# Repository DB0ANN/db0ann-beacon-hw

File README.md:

# db0ann-beacon-hw
Hardware documentation of db0ann beacon

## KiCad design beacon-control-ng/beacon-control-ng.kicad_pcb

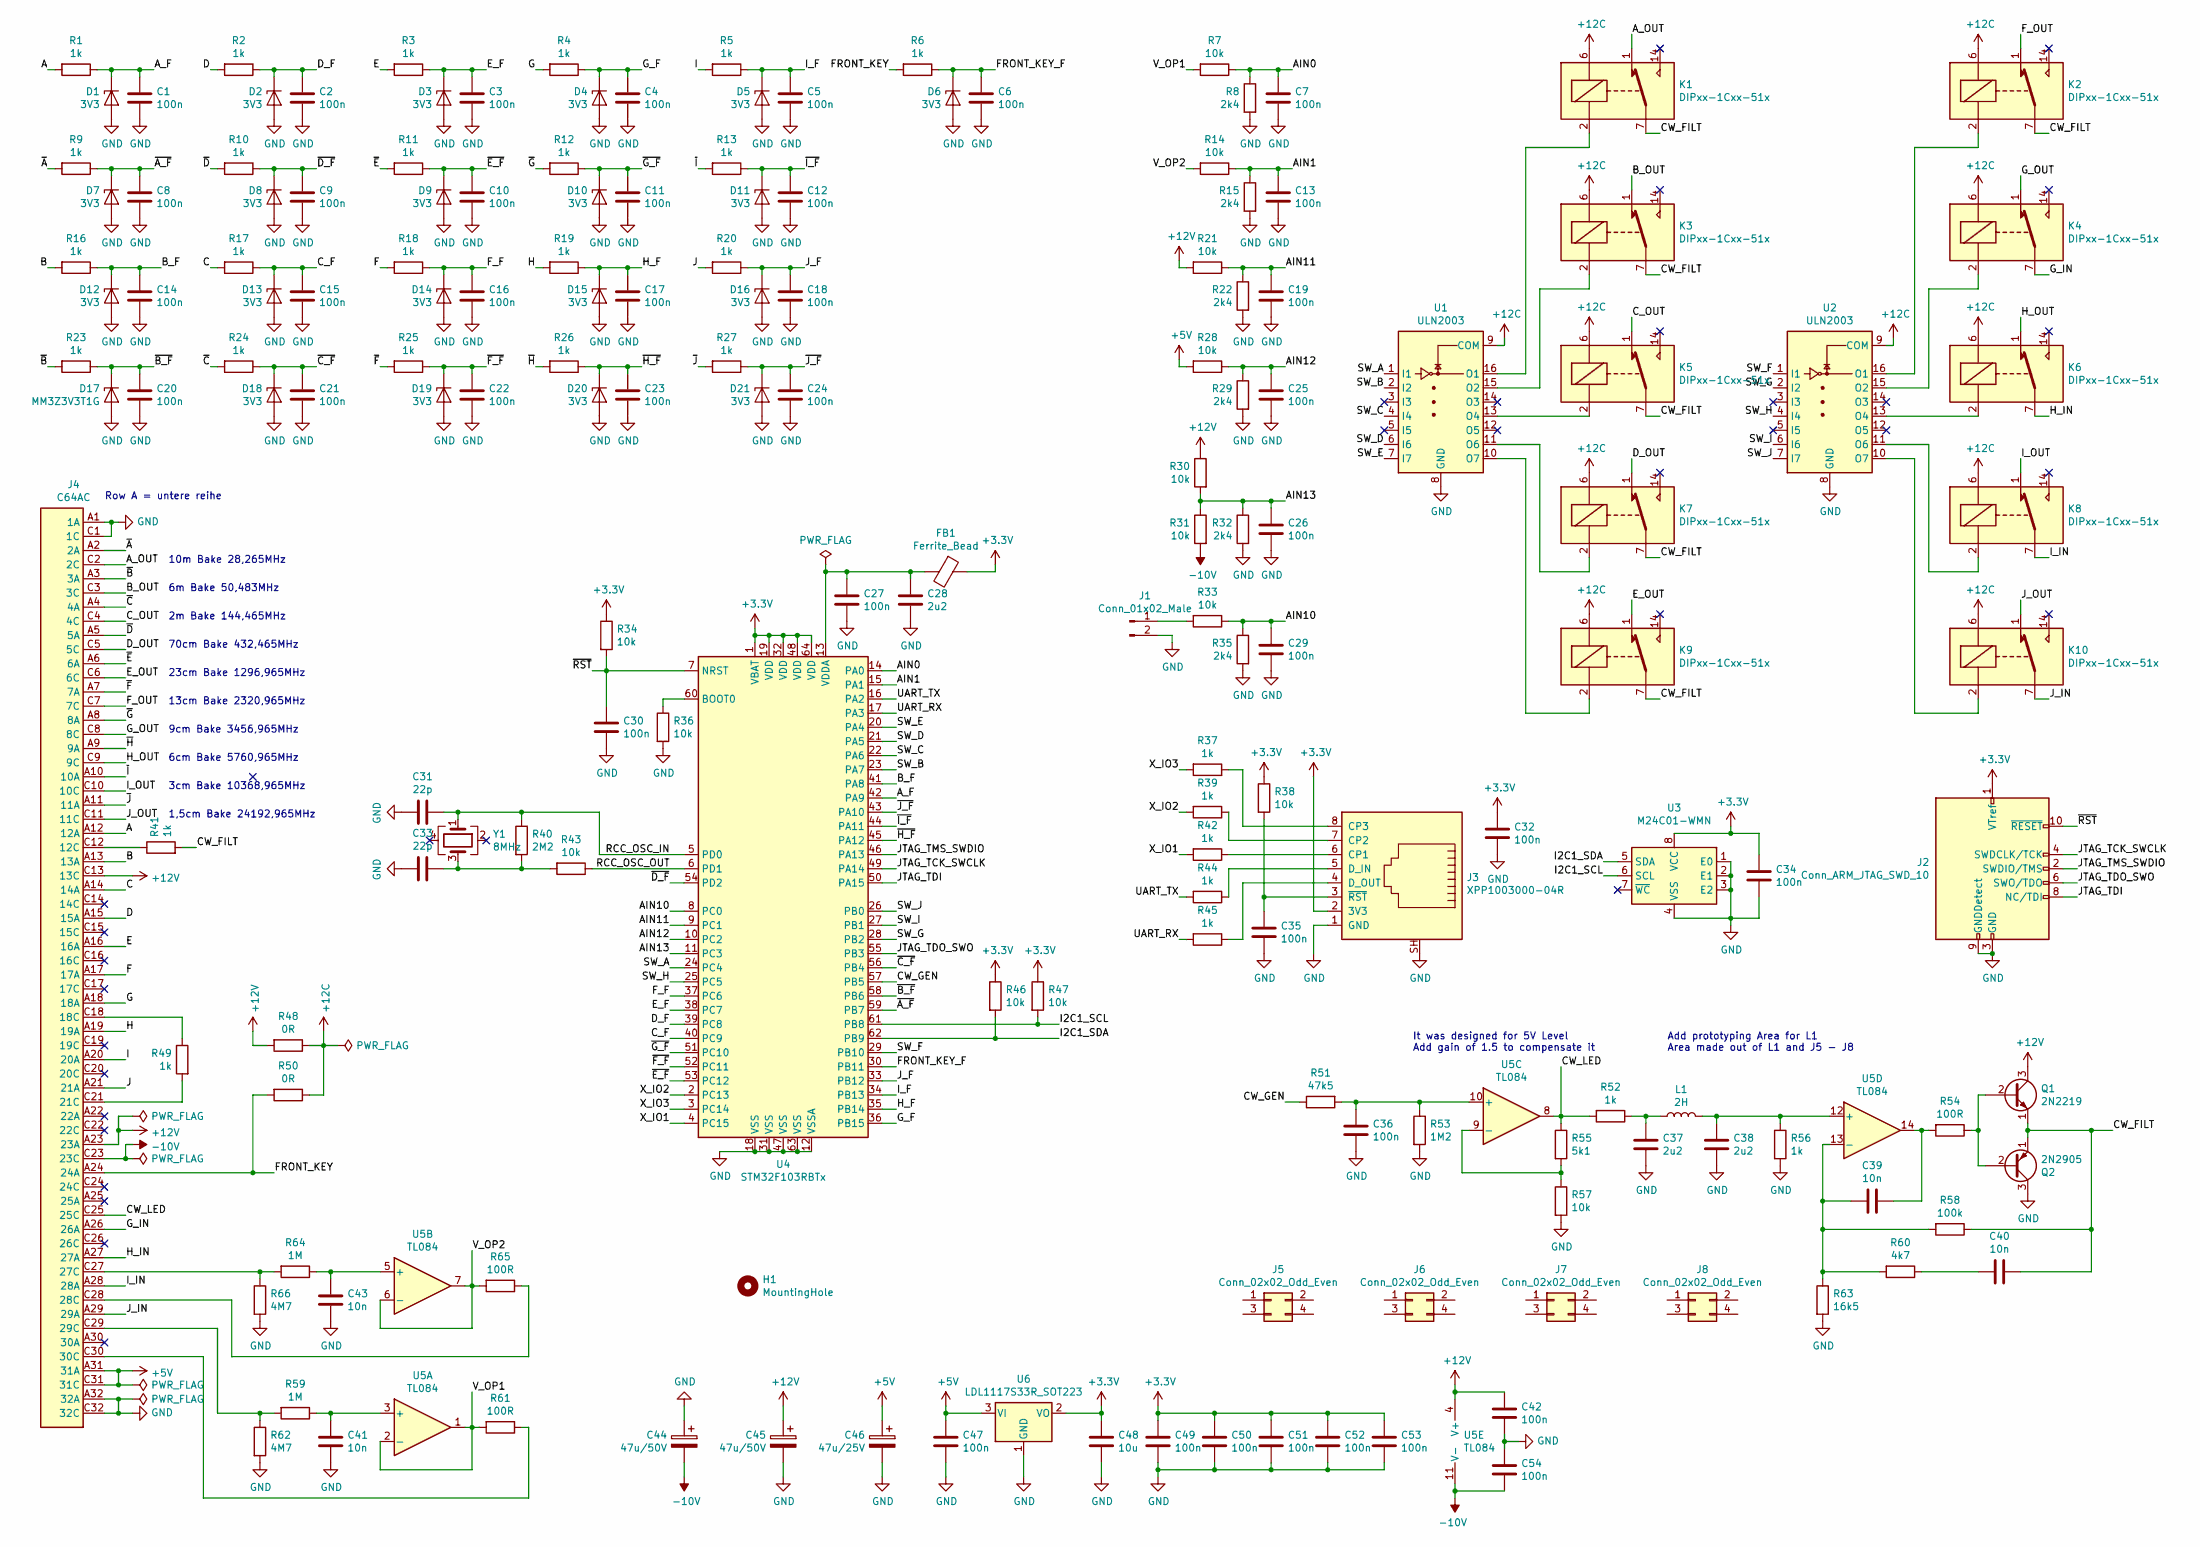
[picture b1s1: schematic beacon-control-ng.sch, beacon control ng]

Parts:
C1, C2, C3, C4, C5, C6, C7, C8, C9, C10, C11, C12, C13, C14, C15, C16, C17, C18, C19, C20, C21, C22, C23, C24, C25, C26, C27, C29, C30, C32, C34, C35, C36, C42, C47, C49, C50, C51, C52, C53, C54: 100n; C_0805_2012Metric
C28, C37, C38: 2u2; C_1206_3216Metric
C31, C33: 22p; C_0805_2012Metric
C39, C40, C41, C43: 10n; C_0805_2012Metric
C44, C45: 47u/50V; CP_Elec_8x10.5
C46: 47u/25V; CP_Elec_8x10.5
C48: 10u; C_1206_3216Metric
D1, D2, D3, D4, D5, D6, D7, D8, D9, D10, D11, D12, D13, D14, D15, D16, D18, D19, D20, D21: 3V3; D_SOD-323
D17: MM3Z3V3T1G; D_SOD-323
FB1: Ferrite_Bead; L_0805_2012Metric
H1: MountingHole; MountingHole_3.2mm_M3
J1: Conn_01x02_Male; PinHeader_1x02_P2.54mm_Vertical
J2: Conn_ARM_JTAG_SWD_10; PinHeader_2x05_P1.27mm_Vertical_SMD
J3: XPP1003000-04R; Lantronix_xPort_Pro
J4: C64AC; DIN41612_C_2x32_Horizontal
J5, J6, J7, J8: Conn_02x02_Odd_Even; PinHeader_2x16_P2.54mm_Vertical
K1, K2, K3, K4, K5, K6, K7, K8, K9, K10: DIPxx-1Cxx-51x; Relay_StandexMeder_DIP_LowProfile
L1: 2H; PinHeader_2x16_P2.54mm_Vertical
Q1: 2N2219; TO-39-3
Q2: 2N2905; TO-39-3
R1, R2, R3, R4, R5, R6, R9, R10, R11, R12, R13, R16, R17, R18, R19, R20, R23, R24, R25, R26, R27, R37, R39, R41, R42, R44, R45, R49, R52, R56: 1k; R_0805_2012Metric
R7, R14, R21, R28, R30, R31, R33, R34, R36, R38, R43, R46, R47, R57: 10k; R_0805_2012Metric
R8, R15, R22, R29, R32, R35: 2k4; R_0805_2012Metric
R40: 2M2; R_0805_2012Metric
R48, R50: 0R; R_0805_2012Metric
R51: 47k5; R_0805_2012Metric
R53: 1M2; R_0805_2012Metric
R54, R61, R65: 100R; R_0805_2012Metric
R55: 5k1; R_0805_2012Metric
R58: 100k; R_0805_2012Metric
R59, R64: 1M; R_0805_2012Metric
R60: 4k7; R_0805_2012Metric
R62, R66: 4M7; R_0805_2012Metric
R63: 16k5; R_0805_2012Metric
U1, U2: ULN2003; SOIC-16_3.9x9.9mm_P1.27mm
U3: M24C01-WMN; SOIC-8_3.9x4.9mm_P1.27mm
U4: STM32F103RBTx; LQFP-64_10x10mm_P0.5mm
U5: TL084; SOIC-14_3.9x8.7mm_P1.27mm
U6: LDL1117S33R_SOT223; SOT-223-3_TabPin2
Y1: 8MHz; Crystal_SMD_EuroQuartz_MQ-4Pin_7.0x5.0mm

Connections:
+3V3: C32.1, C34.1, C48.1, C49.1, C50.1, C51.1, C52.1, C53.1, FB1.1, J2.1 (VTref), J3.2 (3V3), R34.1, R38.1, R46.1, R47.1, U3.8 (VCC), U4.1 (VBAT), U4.19 (VDD), U4.32 (VDD), U4.48 (VDD), U4.64 (VDD), U6.2 (VO)
+5V: C46.1, C47.1, J4.A31 (31A), J4.C31 (31C), R28.2, U6.3 (VI)
+12C: K1.6, K2.6, K3.6, K4.6, K5.6, K6.6, K7.6, K8.6, K9.6, K10.6, R48.1, R50.1, U1.9 (COM), U2.9 (COM)
+12V: C42.1, C45.1, J4.A23 (23A), J4.C13 (13C), Q1.3 (C), R21.2, R30.1, R48.2, U5.4 (V+)
-10V: C44.2, C54.2, J4.C23 (23C), R31.2, U5.11 (V-)
/A: J4.A12 (12A), R1.2
/AIN0: C7.1, R7.1, R8.1, U4.14 (PA0)
/AIN1: C13.1, R14.1, R15.1, U4.15 (PA1)
/AIN10: C29.1, R33.1, R35.1, U4.8 (PC0)
/AIN11: C19.1, R21.1, R22.1, U4.9 (PC1)
/AIN12: C25.1, R28.1, R29.1, U4.10 (PC2)
/AIN13: C26.1, R30.2, R31.1, R32.1, U4.11 (PC3)
/A_F: C1.1, D1.1 (K), R1.1, U4.42 (PA9)
/A_OUT: J4.C2 (2C), K1.1
/B: J4.A13 (13A), R16.2
/B_F: C14.1, D12.1 (K), R16.1, U4.41 (PA8)
/B_OUT: J4.C3 (3C), K3.1
/C: J4.A14 (14A), R17.2
/CW_FILT: C40.1, K1.7, K1.8, K2.7, K2.8, K3.7, K3.8, K5.7, K5.8, K7.7, K7.8, K9.7, K9.8, Q1.1 (E), Q2.1 (E), R41.2, R58.1
/CW_GEN: R51.1, U4.57 (PB5)
/CW_LED: J4.C25 (25C), R52.2, R55.1, U5.8
/C_F: C15.1, D13.1 (K), R17.1, U4.40 (PC9)
/C_OUT: J4.C4 (4C), K5.1
/D: J4.A15 (15A), R2.2
/D_F: C2.1, D2.1 (K), R2.1, U4.39 (PC8)
/D_OUT: J4.C5 (5C), K7.1
/E: J4.A16 (16A), R3.2
/E_F: C3.1, D3.1 (K), R3.1, U4.38 (PC7)
/E_OUT: J4.C6 (6C), K9.1
/F: J4.A17 (17A), R18.2
/FRONT_KEY: J4.A24 (24A), R6.2, R50.2
/FRONT_KEY_F: C6.1, D6.1 (K), R6.1, U4.30 (PB11)
/F_F: C16.1, D14.1 (K), R18.1, U4.37 (PC6)
/F_OUT: J4.C7 (7C), K2.1
/G: J4.A18 (18A), R4.2
/G_F: C4.1, D4.1 (K), R4.1, U4.36 (PB15)
/G_IN: J4.A26 (26A), K4.7, K4.8
/G_OUT: J4.C8 (8C), K4.1
/H: J4.A19 (19A), R19.2
/H_F: C17.1, D15.1 (K), R19.1, U4.35 (PB14)
/H_IN: J4.A27 (27A), K6.7, K6.8
/H_OUT: J4.C9 (9C), K6.1
/I: J4.A20 (20A), R5.2
/I2C1_SCL: R47.2, U3.6 (SCL), U4.61 (PB8)
/I2C1_SDA: R46.2, U3.5 (SDA), U4.62 (PB9)
/I_F: C5.1, D5.1 (K), R5.1, U4.34 (PB13)
/I_IN: J4.A28 (28A), K8.7, K8.8
/I_OUT: J4.C10 (10C), K8.1
/J: J4.A21 (21A), R20.2
/JTAG_TCK_SWCLK: J2.4 (SWDCLK/TCK), U4.49 (PA14)
/JTAG_TDI: J2.8 (NC/TDI), U4.50 (PA15)
/JTAG_TDO_SWO: J2.6 (SWO/TDO), U4.55 (PB3)
/JTAG_TMS_SWDIO: J2.2 (SWDIO/TMS), U4.46 (PA13)
/J_F: C18.1, D16.1 (K), R20.1, U4.33 (PB12)
/J_IN: J4.A29 (29A), K10.7, K10.8
/J_OUT: J4.C11 (11C), K10.1
/RCC_OSC_IN: C31.1, R40.1, U4.5 (PD0), Y1.1
/RCC_OSC_OUT: R43.1, U4.6 (PD1)
/SW_A: U1.1 (I1), U4.24 (PC4)
/SW_B: U1.2 (I2), U4.23 (PA7)
/SW_C: U1.4 (I4), U4.22 (PA6)
/SW_D: U1.6 (I6), U4.21 (PA5)
/SW_E: U1.7 (I7), U4.20 (PA4)
/SW_F: U2.1 (I1), U4.29 (PB10)
/SW_G: U2.2 (I2), U4.28 (PB2)
/SW_H: U2.4 (I4), U4.25 (PC5)
/SW_I: U2.6 (I6), U4.27 (PB1)
/SW_J: U2.7 (I7), U4.26 (PB0)
/UART_RX: R45.2, U4.17 (PA3)
/UART_TX: R44.2, U4.16 (PA2)
/V_OP1: R7.2, R61.2, U5.1, U5.2 (-)
/V_OP2: R14.2, R65.2, U5.6 (-), U5.7
/X_IO1: R42.2, U4.4 (PC15)
/X_IO2: R39.2, U4.2 (PC13)
/X_IO3: R37.2, U4.3 (PC14)
/~A: J4.A2 (2A), R9.2
/~A_F: C8.1, D7.1 (K), R9.1, U4.59 (PB7)
/~B: J4.A3 (3A), R23.2
/~B_F: C20.1, D17.1 (K), R23.1, U4.58 (PB6)
/~C: J4.A4 (4A), R24.2
/~C_F: C21.1, D18.1 (K), R24.1, U4.56 (PB4)
/~D: J4.A5 (5A), R10.2
/~D_F: C9.1, D8.1 (K), R10.1, U4.54 (PD2)
/~E: J4.A6 (6A), R11.2
/~E_F: C10.1, D9.1 (K), R11.1, U4.53 (PC12)
/~F: J4.A7 (7A), R25.2
/~F_F: C22.1, D19.1 (K), R25.1, U4.52 (PC11)
/~G: J4.A8 (8A), R12.2
/~G_F: C11.1, D10.1 (K), R12.1, U4.51 (PC10)
/~H: J4.A9 (9A), R26.2
/~H_F: C23.1, D20.1 (K), R26.1, U4.45 (PA12)
/~I: J4.A10 (10A), R13.2
/~I_F: C12.1, D11.1 (K), R13.1, U4.44 (PA11)
/~J: J4.A11 (11A), R27.2
/~J_F: C24.1, D21.1 (K), R27.1, U4.43 (PA10)
/~RST: C30.1, J2.10 (~RESET~), R34.2, U4.7 (NRST)
GND: C1.2, C2.2, C3.2, C4.2, C5.2, C6.2, C7.2, C8.2, C9.2, C10.2, C11.2, C12.2, C13.2, C14.2, C15.2, C16.2, C17.2, C18.2, C19.2, C20.2, C21.2, C22.2, C23.2, C24.2, C25.2, C26.2, C27.2, C28.2, C29.2, C30.2, C31.2, C32.2, C33.2, C34.2, C35.2, C36.2, C37.2, C38.2, C41.2, C42.2, C43.2, C44.1, C45.2, C46.2, C47.2, C48.2, C49.2, C50.2, C51.2, C52.2, C53.2, C54.1, D1.2 (A), D2.2 (A), D3.2 (A), D4.2 (A), D5.2 (A), D6.2 (A), D7.2 (A), D8.2 (A), D9.2 (A), D10.2 (A), D11.2 (A), D12.2 (A), D13.2 (A), D14.2 (A), D15.2 (A), D16.2 (A), D17.2 (A), D18.2 (A), D19.2 (A), D20.2 (A), D21.2 (A), J1.2, J2.3 (GND), J2.5 (GND), J2.9 (GNDDetect), J3.1 (GND), J3.SH, J4.A1 (1A), J4.A32 (32A), J4.C1 (1C), J4.C32 (32C), Q2.3 (C), R8.2, R15.2, R22.2, R29.2, R32.2, R35.2, R36.2, R53.2, R56.2, R57.2, R62.2, R63.2, R66.2, U1.8 (GND), U2.8 (GND), U3.1 (E0), U3.2 (E1), U3.3 (E2), U3.4 (VSS), U4.12 (VSSA), U4.18 (VSS), U4.31 (VSS), U4.47 (VSS), U4.63 (VSS), U6.1 (GND)
unnamed: C27.1, C28.1, FB1.2, U4.13 (VDDA)
unnamed: C33.1, R40.2, R43.2, Y1.3
unnamed: C35.1, J3.3 (~RST), R38.2
unnamed: C36.1, R51.2, R53.1, U5.10 (+)
unnamed: C37.1, L1.1, R52.1
unnamed: C38.1, L1.2, R56.1, U5.12 (+)
unnamed: C39.1, R54.2, U5.14
unnamed: C39.2, R58.2, R60.2, R63.1, U5.13 (-)
unnamed: C40.2, R60.1
unnamed: C41.1, R59.1, U5.3 (+)
unnamed: C43.1, R64.1, U5.5 (+)
unnamed: J1.1, R33.2
unnamed: J3.4 (D_OUT), R45.1
unnamed: J3.5 (D_IN), R44.1
unnamed: J3.6 (CP1), R42.1
unnamed: J3.7 (CP2), R39.1
unnamed: J3.8 (CP3), R37.1
unnamed: J4.C12 (12C), R41.1
unnamed: J4.C18 (18C), R49.1
unnamed: J4.C21 (21C), R49.2
unnamed: J4.C27 (27C), R64.2, R66.1
unnamed: J4.C28 (28C), R65.1
unnamed: J4.C29 (29C), R59.2, R62.1
unnamed: J4.C30 (30C), R61.1
unnamed: K1.2, U1.16 (O1)
unnamed: K2.2, U2.16 (O1)
unnamed: K3.2, U1.15 (O2)
unnamed: K4.2, U2.15 (O2)
unnamed: K5.2, U1.13 (O4)
unnamed: K6.2, U2.13 (O4)
unnamed: K7.2, U1.11 (O6)
unnamed: K8.2, U2.11 (O6)
unnamed: K9.2, U1.10 (O7)
unnamed: K10.2, U2.10 (O7)
unnamed: Q1.2 (B), Q2.2 (B), R54.1
unnamed: R36.1, U4.60 (BOOT0)
unnamed: R55.2, R57.1, U5.9 (-)

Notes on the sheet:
Row A = untere reihe
It was designed for 5V Level Add gain of 1.5 to compensate it
10m Bake 28,265MHz
6m Bake 50,483MHz
70cm Bake 432,465MHz
2m Bake 144,465MHz
23cm Bake 1296,965MHz
13cm Bake 2320,965MHz
9cm Bake 3456,965MHz
6cm Bake 5760,965MHz
3cm Bake 10368,965MHz
1,5cm Bake 24192,965MHz
Add prototyping Area for L1 Area made out of L1 and J5 - J8

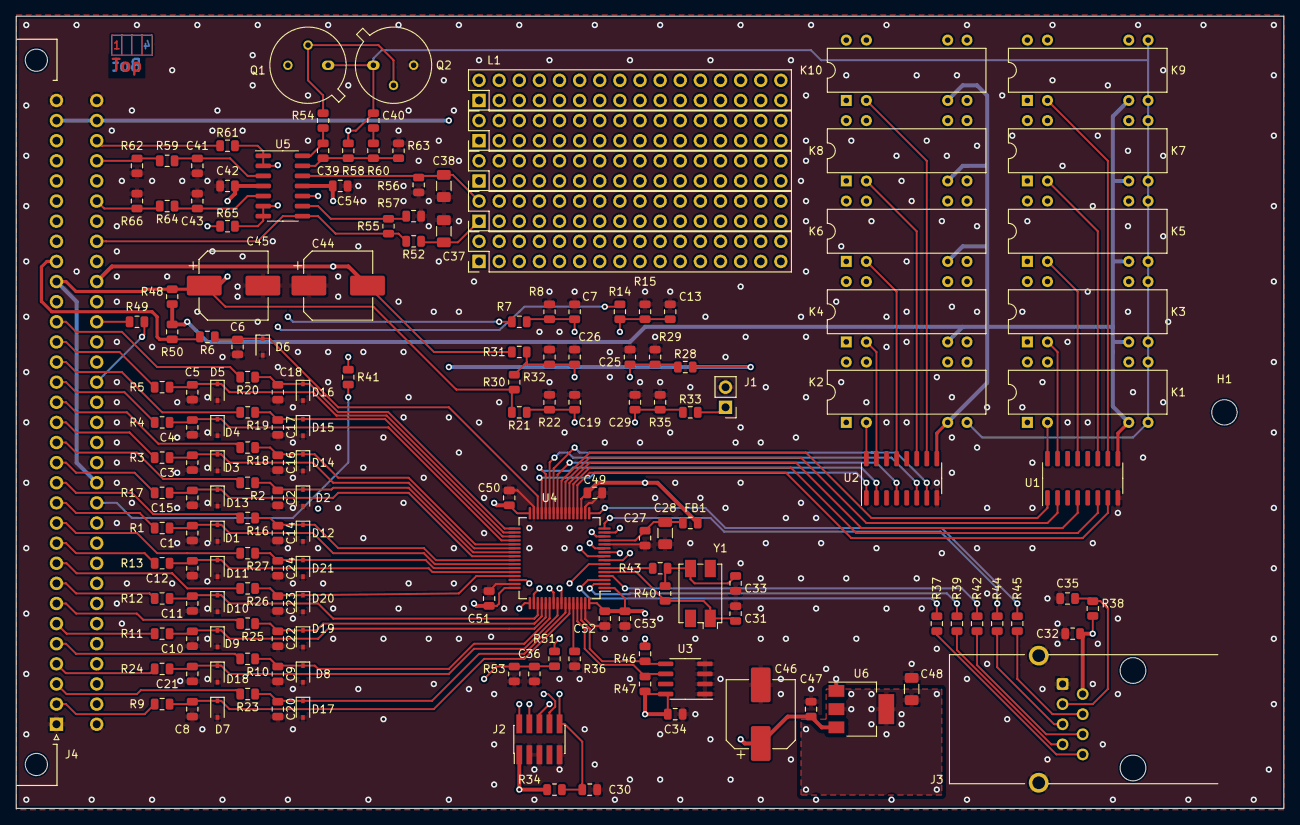
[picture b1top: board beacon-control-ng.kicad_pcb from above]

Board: 4 copper layers, 160.0 x 100.0 mm, 171 parts (0 on the bottom side), 134 nets.

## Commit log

2020-03-16 wip reverse engineering of control unit
2020-03-17 some more reverse engineering
2020-03-20 Finished reverse engineering
2020-03-20 Some refactoring
2020-03-21 Add missing part values
2020-04-01 Add lib with custom parts for this project
2020-04-01 First draft of new beacon control hw
2020-04-10 Add design document + small schematic fixes
2020-04-10 Reformat Design for github rendering
2020-05-03 Commit layout work in progress
2020-06-11 Finished layout
2020-06-11 Update pinning list after layout
2020-06-21 Place designators on assembly printing
